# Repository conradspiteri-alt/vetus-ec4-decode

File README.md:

# vetus-ec4-can

An independent, listen-only decode of the CAN bus inside a **Vetus EC4** electronic engine control (made by Flexball Italiana, 4500 series), plus the isolated sniffer hardware and firmware that captured it.

Version 0.2, October 2026. By Dr.FireFly.

> Listen only. Do not transmit on an engine-control bus. See `NOTICE.md`.

## What is decoded

- 125 kbit/s, 11-bit IDs, CANopen-like, no master. Eight IDs: two station frames (0x181, 0x282), two actuator status bytes (0x384, 0x485), four heartbeats.
- Station frame byte map: flags, gear (FF ahead, 00 neutral, 01 astern) and throttle (0 to 100 %) for each engine. Both heads broadcast their levers at all times; the gearboxes follow the head in command.
- Actuator status: C0 neutral, 4C shifting, 44 ahead, 48 astern, 40 booting.
- Boot sequence, warm-up, synchronisation, and lever-to-gear timing including labelled fast reversals.

Some findings are not in this release: they are being disclosed to the manufacturers first.

New to this? Start with `docs/examples.md`: ahead and astern at each helm, one picture each. Then `docs/protocol.md` for the decode, and `docs/events.md` for a full sequence from power-on to fast reversals.

## Layout

| Path | What |
|---|---|
| `docs/examples.md` | Simple examples: ahead and astern at each helm, one annotated picture each |
| `docs/protocol.md` | The decode, with every value tagged measured, inferred or from the manual |
| `docs/events.md` | Event gallery: the sample capture in the viewer at nine key moments |
| `docs/background-research.md` | Desk research before the first capture (sources linked) |
| `docs/capture-procedures/` | Step lists used for captures 2 and 3 |
| `dbc/ec4.dbc` | DBC for SavvyCAN and cantools; every message observed |
| `data/reference/*.csv` | Reference tables: IDs and timing, byte maps, codes, boot, every shift event, reversals, findings, captures |
| `captures/` | candump logs with phone notes, and `sample/ec4-sample.log`, the viewer's built-in sample |
| `tools/` | Log reader, statistics, DBC validator, replay extractor, secrets check, browser playback viewer |
| `firmware/sniffer/` | ESP32-S3 listen-only logger firmware. Edit `secrets.h` before flashing |
| `hardware/sniffer/` | Carrier PCB (KiCad, gerbers), enclosure (OpenSCAD, STL, drawings), wiring diagrams, full BOM including the Vetus CANT T-piece |

## Viewer

Open `tools/lever-playback/dist/EC4-Lever-Playback.html` after building it, or build it with `python3 tools/lever-playback/build.py`. It opens on the sample capture; load any sniffer log with "Open log file".

## Quick checks

```
pip install cantools
python3 tools/validate_dbc.py                       # decodes the published captures with the DBC
python3 tools/log_stats.py                          # periods, boots, gear response, bus load
python3 hardware/sniffer/tools/check_netlist.py     # PCB nets against the firmware pin map
python3 tools/check_secrets.py                      # run before every commit
python3 tools/lever-playback/build.py               # builds dist/EC4-Lever-Playback.html with the sample built in
python3 tools/lever-playback/screenshots.py         # regenerates docs/images/events (needs Playwright)
```

## Installation the data comes from

A Fairline Phantom 42, twin Volvo Penta TAMD63P, owner-installed EC4 with every parameter at factory default, two twin-lever heads (main helm and flybridge), two actuator boxes. Engines off in every capture.

## Licence

Code: MIT (`LICENSE`). Documentation, data and hardware design files: CC BY 4.0 (`LICENSE-DOCS.md`). Dr.FireFly, 2026.

## Contributing captures

Captures from other EC4 installations are the most useful contribution: one labelled step per note, engines off, listen-only. The procedures in `docs/capture-procedures/` are a template.

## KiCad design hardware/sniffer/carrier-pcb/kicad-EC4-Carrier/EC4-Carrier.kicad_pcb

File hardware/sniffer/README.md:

# Listen-only EC4 sniffer: hardware

A galvanically isolated, listen-only CAN logger that plugs into the Vetus EC4 bus through the OEM T-piece, logs every frame to microSD in candump format, and serves the logs over WiFi. It produced every capture in this repository.

> Listen-only by design: the CAN controller runs in TWAI listen-only mode and never transmits, acknowledges or sends error frames. Nothing on the bus is reconfigured: no DIP switch, no JP19, no address, no terminator.

## Contents

| Path | What |
|---|---|
| `BOM.csv`, table below | Every part needed to build one unit, including the T-piece (Y-cable), power and enclosure hardware |
| `tap.md` | How the T-piece goes into the bus, and the isolation rule |
| `carrier-design-brief.md` | Carrier PCB rev B design record: board data, net list, mechanical, verification, enclosure rev B, sealed-build notes |
| `carrier-pcb/kicad-EC4-Carrier/` | KiCad project, KiCad 7 file format (20221018). The title block still reads rev A; the layout is rev B (88 x 74 mm). Opening in a newer KiCad converts it on save |
| `carrier-pcb/EC4-Carrier-revB-gerbers.zip` | Fabrication files as ordered, 2-layer, 1.6 mm |
| `carrier-pcb/*.svg`, `EC4-Carrier-Drawing.pdf` | Concept, layout, schematic and dimensioned drawing |
| `enclosure/EC4-Enclosure.scad` | OpenSCAD source, enclosure rev B |
| `enclosure/*.stl` | Base and lid, print-ready |
| `enclosure/EC4-Enclosure-Drawing.pdf`, `-Views.png` | Dimensioned drawing and renders |
| `diagrams/` | Wiring (pin-accurate), harness pinout, circuit, block diagram, housing layout |
| `tools/check_netlist.py` | Checks the PCB nets against the GPIO numbers in the firmware. `python3 tools/check_netlist.py` |

Firmware: `../../firmware/sniffer/`.

## Architecture

ESP32-S3-DevKitC-1 (TWAI listen-only, SD logging, WiFi HTTP and GVRET for SavvyCAN) on a carrier PCB with an SK Pang ISO1050 isolated CAN board and a microSD breakout. Power: a USB-A power bank into a 5 V screw terminal through a PTC fuse, series Schottky and TVS. The bus side is isolated by the ISO1050 and its own isolated DC-DC; the power bank floats, so the barrier is real.

**Isolation rule.** If the unit is ever fed from boat 12 V, use an isolated 12 V to 5 V converter upstream of J2. A non-isolated buck ties the logic side to boat negative, which is also the EC4 bus ground, and the barrier stops meaning anything.

## Bill of materials

One unit. Line cost is what you pay, so parts sold in packs carry the pack price. Prices GBP ex VAT; "est." lines are indicative, others are supplier prices of September 2026.

| Group | Ref | Qty | Part | Manufacturer / part no. | Supplier | Line £ | Basis | Notes |
|---|---|---|---|---|---|---|---|---|
| Bus tap (Y-cable) | T1 | 1 | CAN-bus T-piece M12 A-coded 5-pin (2 female + 1 male) | Vetus CANT | vetus-shop.com | 50.83 | Supplier list 8 Sep 2026 | The Y-cable. Inline in an interior DTCAN link; the box plugs onto the spare female. Passes the bus straight through |
| Bus tap (Y-cable) | X1 | 1 | M12 A-coded 5-pin male panel connector IP67 with leads or solder cups | Any (match the panel hole in the enclosure) |  | 8.00 | est. | Plugs directly onto the CANT spare female. Only CAN_H (black) and CAN_L (blue) and 0 V (brown) are wired. +24 V (white) and pin 5 (grey) capped |
| Bus tap (Y-cable) | W1 | 0.2 m | Twisted pair 0.25 to 0.5 mm2 tinned | Any |  | 0.50 | est. | X1 to the SK Pang 3-way CAN terminal. Ferrules on the screw-terminal ends |
| Bus tap (Y-cable) | X2 | 0 | M12 A-coded 5-pin male-female extension 0.3 to 1 m | Any |  | 0.00 | est. | Optional. Only if the box cannot sit on the T. Keep the stub under 1 m |
| Electronics | U1 | 1 | ESP32-S3-DevKitC-1 v1.1 (N8 or N16R8) with headers fitted | Espressif ESP32-S3-DevKitC-1 | Any | 14.00 | est. | Soldered pins-down into the carrier. Antenna end over the board notch |
| Electronics | U2 | 1 | Isolated CAN breakout 3.3 V (TI ISO1050 with isolated DC-DC) | SK Pang Electronics isolated CAN-Bus breakout rev B 06/18 | skpang.co.uk | 31.50 | Supplier list 8 Sep 2026 | No terminator fitted (54.6 kohm measured across CAN_H/CAN_L). 3.3 V logic jumper confirmed |
| Electronics | U3 | 1 | microSD breakout SPI 9-pin with pull-ups | SB Components microSD card breakout | Any | 5.00 | est. | Silkscreen uses SDIO names; carrier silk shows the SPI names |
| Electronics | SD1 | 1 | microSD card 8 to 32 GB FAT32 (high-endurance preferred) | Any |  | 6.00 | est. | Files roll at 8 MB |
| Electronics | PCB1 | 1 | Carrier PCB rev B 88 x 74 mm L-shape 2-layer 1.6 mm 1 oz HASL | Gerbers: carrier-pcb/EC4-Carrier-revB-gerbers.zip | JLCPCB or PCBWay | 7.73 | PCBWay 16 Sep 2026: USD 10.24 for 5 at 1.3252 | Minimum order 5 |
| Electronics | F1 | 1 | PTC fuse 1.1 A hold 2.2 A trip 30 V radial 5.08 mm | Bourns MF-R110 | RS 647-8522 | 2.59 | RS 16 Sep 2026 |  |
| Electronics | D2 | 1 | Schottky 40 V 1 A DO-41 | onsemi 1N5819G | RS 774-3347 | 1.40 | RS 16 Sep 2026 | Series diode; stops J2 back-feeding a USB host |
| Electronics | D1 | 1 | TVS 600 W 6.8 V bidirectional DO-15 | ST P6KE6V8CA | RS 486-1130 | 4.57 | RS 16 Sep 2026 | Bidirectional on purpose (no polarity error). Do not use SA5.0A (conducts at power-bank voltage) |
| Electronics | C1 | 1 | Electrolytic 100 uF 16 V 6.3 x 11 mm 2.5 mm pitch | Panasonic ECA1CM101 | RS 228-6650 | 0.90 | RS 16 Sep 2026 |  |
| Electronics | C2 | 1 | Ceramic 100 nF 50 V X7R 5.08 mm | Vishay K104K15X7RF5TH5 | RS 852-3277 | 1.00 | RS 16 Sep 2026 |  |
| Electronics | J2 | 1 | 2-way PCB screw terminal 3.50 mm pitch (3.81 also fits) | Phoenix Contact MKDS 1/2-3.5 | RS 467-0259 | 0.60 | est. | 5.08 mm pitch does NOT fit the pads |
| Electronics | J3 | 1 | Male pin header 1 x 4 2.54 mm | Any |  | 0.20 | est. | SK Pang to carrier |
| Electronics | J4 | 1 | Male pin header 1 x 9 2.54 mm | Any |  | 0.20 | est. | microSD to carrier |
| Power | PB1 | 1 | USB power bank USB-A output 5 V 10000 mAh or more | Any |  | 15.00 | est. | Floating supply keeps the isolation barrier meaningful. About 40 h at about 150 mA (est.) |
| Power | W2 | 1 | USB-A lead cut to bare wire 1 m | Any |  | 2.00 | est. | Meter which conductor is +5 V before terminating on J2 |
| Power | G1 | 1 | Cable gland M12 3 to 6.5 mm IP68 with locknut | RS PRO | RS 669-4654 | 5.04 | RS 16 Sep 2026 | Power lead entry. 12.5 mm panel hole |
| Power | FER | 6 | Bootlace ferrules 0.5 mm2 | Any |  | 0.20 | est. | J2 and the SK Pang CAN terminal |
| Enclosure | ENC1 | 1 | Enclosure base and lid 3D printed (enclosure/EC4-Enclosure-base.stl and -lid.stl) | Print |  | 2.50 | est. (about 100 g filament) | ASA or PETG for an engine space; the test unit was PLA. 4+ perimeters if sealed |
| Enclosure | INS | 6 | M3 brass heat-set inserts (4.0 mm hole) | Any |  | 0.60 | est. | 4 for the corner bosses; 6 if adding mid-span lid screws |
| Enclosure | SCR1 | 6 | M3 x 12 lid screws A4 stainless | Any |  | 0.50 | est. | 4 or 6 as above |
| Enclosure | SCR2 | 2 | M3 screws with nuts or inserts (SK Pang holes) | Any |  | 0.20 | est. | Printed spacers at the measured seated header height |
| Enclosure | SCR3 | 2 | M2 screws with nuts (microSD far holes only) | Any |  | 0.20 | est. | Printed spacers at the measured seated header height |
| Enclosure | SO1 | 1 | 6 mm bonded standoff under the SK Pang DB9 end | Print or nylon spacer |  | 0.10 | est. | Mandatory. Bond with epoxy or CA. No screw |
| Enclosure | FOAM | 1 | EVA foam sheet 1.5 mm | Any |  | 0.50 | est. | Lid hold-down pads and rib: the clamp that stops the board buzzing |
| Enclosure (sealed build) | SEAL | 0.4 m | Silicone cord 2 to 3 mm | Any |  | 4.00 | est. | In a 2.2 x 2.5 mm lid groove |
| Enclosure (sealed build) | VENT | 1 | Pressure-equalising vent membrane IP67 (ePTFE) | Any (Gore-type) |  | 5.00 | est. | Stops the box pumping damp air through the seal |
| Installation | MNT | 1 | Bracket or ties to structure | Any |  | 1.00 | est. | The box must not hang on the M12 joint |
| Tools and consumables | - | - | Solder; heat-shrink; multimeter; Arduino IDE 2.x with esp32 by Espressif 3.x | Owner |  | 0.00 |  | Meter CAN_H to CAN_L (about 60 to 67 ohm EC4 off) and continuity connector-to-transceiver before trusting a capture |

| Group | GBP ex VAT |
|---|---|
| Bus tap (T-piece, panel connector, wire) | 59.33 |
| Electronics | 75.69 |
| Power | 22.24 |
| Enclosure | 4.60 |
| Sealed-build extras | 9.00 |
| Installation | 1.00 |
| **Total** | **about 172** |

## Build notes that matter

- **J2 pitch.** The pads take a 3.50 or 3.81 mm terminal. The 5.08 mm terminal found in most parts drawers does not fit.
- **Spacer height** for the SK Pang and microSD equals the seated header height. Measure it; do not assume 2.5 mm.
- **The 6 mm bonded standoff under the SK Pang DB9 end is mandatory.** Both of its holes are on the header edge, so the board is a 50 mm cantilever with the DB9 mass on the end; engine vibration excites it.
- **Firmware setting:** USB CDC On Boot DISABLED; flash through the UART connector.
- **Before any capture:** meter about 60 to 67 ohm across CAN_H and CAN_L with the EC4 off, and check continuity from each M12 pin to the transceiver. An open CAN_L still receives, badly: see `docs/protocol.md` section 9.

## Enclosure: source against the as-built unit

`EC4-Enclosure.scad` and the STLs are **rev B**: a UART port opening (12 x 9 mm), a 16 x 11 mm opening for the M12 tail, a 13 x 10 mm power slot and a 0.6 mm LED window in a 2.5 mm lid. The unit on the boat was built sealed: panel-mount M12, a 12.5 mm hole for the M12 power gland, no port opening and a 5 mm solid lid with no window (firmware README). Those changes are not in the source. Treat the STLs as the rev B baseline and cut the sealed-build holes to suit the panel connector you fit.

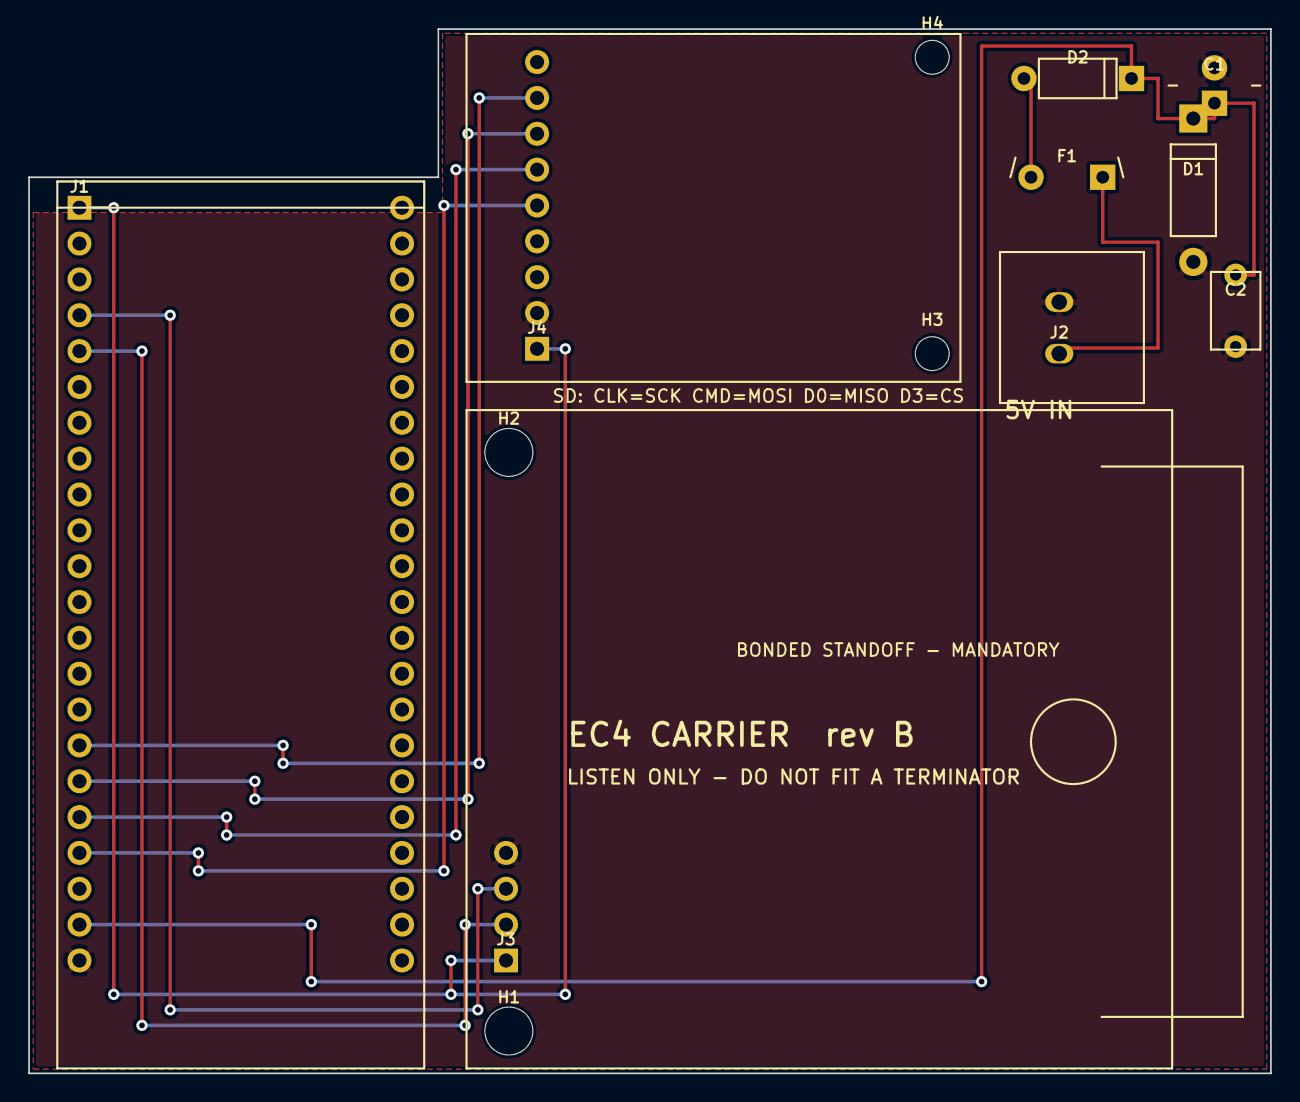
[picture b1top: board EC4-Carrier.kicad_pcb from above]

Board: 2 copper layers, 88.0 x 74.0 mm, 13 parts (0 on the bottom side), 11 nets.

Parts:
C1: 100uF-16V-radial-2.5; C1
C2: 100nF-5.08; C2
D1: P6KE6.8A-DO15-10.16; D1
D2: 1N5819-DO41-7.62; D2
F1: PTC-1A-radial-5.08; F1
H1, H2: 3.4mm; MountingHole
H3, H4: 2.4mm; MountingHole
J1: ESP32-S3-DevKitC-1; J1
J2: TerminalBlock_2x3.5mm; J2
J3: SKPang-ISO1050; J3
J4: microSD-SB; J4

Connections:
+3V3: J1.1, J3.1, J4.1
+5V: C1.1, C2.1, D1.2, D2.2, J1.21
CAN_RX: J1.4, J3.3
CAN_TX: J1.5, J3.2
GND: C1.2, C2.2, D1.1, J1.22, J2.2, J3.4, J4.2
SD_CS: J1.16, J4.8
SD_MISO: J1.19, J4.5
SD_MOSI: J1.17, J4.7
SD_SCK: J1.18, J4.6
VF: D2.1, F1.2
VIN: F1.1, J2.1

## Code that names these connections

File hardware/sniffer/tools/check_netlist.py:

#!/usr/bin/env python3
"""
EC4 sniffer carrier - firmware / PCB net-list correlation check.

Reads the pin assignments straight out of the firmware source, maps them to
ESP32-S3-DevKitC-1 header pin numbers using Espressif's official J1 table, then
reads the actual pad nets out of the KiCad board file and compares.

Nothing here is typed by hand twice. Re-run it after ANY change to either file.

    python3 tools/check_netlist.py

Sources for the J1 table:
  https://documentation.espressif.com/esp-dev-kits/en/latest/esp32s3/esp32-s3-devkitc-1/user_guide_v1.1.html
"""
import re, sys, os

HERE = os.path.dirname(os.path.abspath(__file__))
REPO = os.path.abspath(os.path.join(HERE, "..", "..", ".."))
INO  = os.path.join(REPO, "firmware", "sniffer", "ec4_can_sniffer", "ec4_can_sniffer.ino")
PCB  = os.path.join(REPO, "hardware", "sniffer", "carrier-pcb", "kicad-EC4-Carrier", "EC4-Carrier.kicad_pcb")

# ---------------------------------------------------------------- J1 pin table
# ESP32-S3-DevKitC-1 v1.1, Header J1, pin no. -> signal.
# Taken from the Function column of Espressif's table, NOT the Name column
# (the Name column renders ambiguously in some mirrors of the doc).
J1 = {1:"3V3", 2:"3V3", 3:"RST", 4:"GPIO4", 5:"GPIO5", 6:"GPIO6", 7:"GPIO7",
      8:"GPIO15", 9:"GPIO16", 10:"GPIO17", 11:"GPIO18", 12:"GPIO8", 13:"GPIO3",
      14:"GPIO46", 15:"GPIO9", 16:"GPIO10", 17:"GPIO11", 18:"GPIO12",
      19:"GPIO13", 20:"GPIO14", 21:"5V", 22:"GND"}
SIG2PIN = {}
for n, s in J1.items():
    SIG2PIN.setdefault(s, n)          # 3V3 appears twice; first occurrence wins

# firmware symbol -> the carrier net it must land on
EXPECT_NET = {"PIN_CAN_TX":"CAN_TX", "PIN_CAN_RX":"CAN_RX", "PIN_SD_SCK":"SD_SCK",
              "PIN_SD_MOSI":"SD_MOSI", "PIN_SD_MISO":"SD_MISO", "PIN_SD_CS":"SD_CS"}
# rails that are not in the firmware but must still be right
RAILS = {"3V3":"+3V3", "5V":"+5V", "GND":"GND"}

# ---------------------------------------------------------------- parse firmware
src = open(INO).read()
fw = {}
for m in re.finditer(r'(PIN_[A-Z_]+)\s*=\s*GPIO_NUM_(\d+)', src):
    fw[m.group(1)] = int(m.group(2))
for m in re.finditer(r'(PIN_[A-Z_]+)\s*=\s*(\d+)\s*[,;]', src):
    fw.setdefault(m.group(1), int(m.group(2)))

# also confirm the SPI bus really is begun in the SCK, MISO, MOSI, CS order
spi = re.search(r'sdSPI\.begin\(\s*([A-Z_]+)\s*,\s*([A-Z_]+)\s*,\s*([A-Z_]+)\s*,\s*([A-Z_]+)\s*\)', src)

# ---------------------------------------------------------------- parse the PCB
pcb = open(PCB).read()
i = pcb.find('(footprint "ec4:J1"')
d, j = 0, i
while True:
    if pcb[j] == "(": d += 1
    elif pcb[j] == ")":
        d -= 1
        if d == 0: break
    j += 1
blk = pcb[i:j+1]
def _span(text, start):
    """Return the substring of the balanced s-expression beginning at `start`."""
    d, j = 0, start
    while True:
        if text[j] == "(": d += 1
        elif text[j] == ")":
            d -= 1
            if d == 0: return text[start:j+1]
        j += 1

pcb_net, k = {}, 0
while True:
    k = blk.find('(pad "', k)
    if k < 0: break
    pad = _span(blk, k); k += 1
    num = re.match(r'\(pad "([^"]+)"', pad).group(1)
    if not num.isdigit(): continue
    nm = re.search(r'\(net \d+ "([^"]*)"\)', pad)
    pcb_net[int(num)] = nm.group(1) if nm else ""

# ------------------------------------------------ destination module pin tables
# Read off the boards themselves (silkscreen), not from a datasheet.
# SK Pang Rev B 06/18 host header, pin 1 = the pad nearest the +Vcc end.
J3_LABEL = {1:"+Vcc", 2:"CAN_TX", 3:"CAN_RX", 4:"GND"}
J3_EXPECT = {1:"+3V3", 2:"CAN_TX", 3:"CAN_RX", 4:"GND"}
# SB Components microSD breakout. Silkscreen uses SDIO names; the SPI role is what matters.
J4_LABEL = {1:"3V3", 2:"GND", 3:"CD", 4:"D1", 5:"D0", 6:"CLK", 7:"CMD", 8:"D3", 9:"D2"}
J4_EXPECT = {1:"+3V3", 2:"GND", 3:"", 4:"", 5:"SD_MISO", 6:"SD_SCK", 7:"SD_MOSI", 8:"SD_CS", 9:""}
J4_ROLE  = {5:"MISO", 6:"SCK", 7:"MOSI", 8:"CS"}

def pads_of(ref):
    a = pcb.find(f'(footprint "ec4:{ref}"')
    b = _span(pcb, a)
    out, k = {}, 0
    while True:
        k = b.find('(pad "', k)
        if k < 0: return out
        pad = _span(b, k); k += 1
        num = re.match(r'\(pad "([^"]+)"', pad).group(1)
        if not num.isdigit(): continue
        nm = re.search(r'\(net \d+ "([^"]*)"\)', pad)
        out[int(num)] = nm.group(1) if nm else ""

# ---------------------------------------------------------------- compare
rows, bad = [], 0
def row(sym, sig, pin, want, got):
    global bad
    ok = (want == got)
    if not ok: bad_inc()
    rows.append((sym, sig, pin, want, got, "OK" if ok else "*** MISMATCH ***"))
def bad_inc():
    global bad; bad += 1

for sym, net in EXPECT_NET.items():
    if sym not in fw:
        rows.append((sym, "-", "-", net, "NOT FOUND IN FIRMWARE", "*** MISSING ***")); bad_inc(); continue
    sig = f"GPIO{fw[sym]}"
    pin = SIG2PIN.get(sig)
    if pin is None:
        rows.append((sym, sig, "-", net, "NOT ON HEADER J1", "*** MISMATCH ***")); bad_inc(); continue
    row(sym, sig, pin, net, pcb_net.get(pin, "<no net>"))
for sig, net in RAILS.items():
    pin = SIG2PIN[sig]
    row("(rail)", sig, pin, net, pcb_net.get(pin, "<no net>"))

# destination side
dst = []
for ref, lab, exp, role in (("J3", J3_LABEL, J3_EXPECT, {}), ("J4", J4_LABEL, J4_EXPECT, J4_ROLE)):
    got = pads_of(ref)
    for pin in sorted(lab):
        want = exp[pin]; have = got.get(pin, "<no pad>")
        ok = (want == have) or (want == "" and have == "")
        if not ok: bad_inc()
        r = role.get(pin, "")
        dst.append((f"{ref}.{pin}", lab[pin] + (f" ({r})" if r else ""),
                    want or "(none)", have or "(none)", "OK" if ok else "*** MISMATCH ***"))

w = max(len(r[0]) for r in rows)
print(f"{'firmware':<{w}}  {'signal':<7} {'J1 pin':>6}  {'expected net':<12} {'net on PCB':<12}  result")
print("-" * (w + 60))
for r in rows:
    print(f"{r[0]:<{w}}  {str(r[1]):<7} {str(r[2]):>6}  {r[3]:<12} {str(r[4]):<12}  {r[5]}")

print()
w2 = max(len(r[0]) for r in dst)
print(f"{'module pad':<{w2}}  {'silkscreen':<14} {'expected net':<12} {'net on PCB':<12}  result")
print("-" * (w2 + 58))
for r in dst:
    print(f"{r[0]:<{w2}}  {r[1]:<14} {r[2]:<12} {r[3]:<12}  {r[4]}")

print()
if spi:
    order = spi.groups()
    want = ("PIN_SD_SCK", "PIN_SD_MISO", "PIN_SD_MOSI", "PIN_SD_CS")
    print(f"SPI bus begin order: {', '.join(order)}   ->  "
          + ("OK (SCK, MISO, MOSI, CS)" if order == want else "*** CHECK: expected SCK, MISO, MOSI, CS ***"))
    if order != want: bad_inc()
else:
    print("SPI bus begin call not found  *** CHECK ***"); bad_inc()

# SD silkscreen name trap: carrier pads must carry SPI names, board prints SDIO names
print("SDIO -> SPI mapping on the microSD breakout: CLK=SCK, CMD=MOSI, D0=MISO, D3=CS")

print()
print("NET-LIST CORRELATION: PASS" if bad == 0 else f"NET-LIST CORRELATION: {bad} PROBLEM(S)")
sys.exit(0 if bad == 0 else 1)
